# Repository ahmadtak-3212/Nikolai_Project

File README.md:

# Nikolai: electromagnet gauntlet

Nikolai is a 3D-printed gauntlet with a hand-wound **electromagnet in the palm**, so the wearer can pick up and hold ferromagnetic objects. It has three main parts:

- an ESP32 on the wrist that controls coil power with PWM and shows a touchscreen UI;
- a MOSFET coil driver that measures coil current and temperature;
- a small web server that stores per-user safety limits and logs sensor data.

It was a five-person team project for MIT **6.08** (Interconnected Embedded Systems) in spring 2022.

## Team

James Adams, Daven Howard, Sebastian Portalatin, **Ahmad Taka** and Colin Tang.

## Status

| Area | Status |
|---|---|
| Electrical | ✅ Coil driver v1 and v2 and the wrist PCB, all routed with Gerbers; schematic PDFs in `electrical/` |
| Firmware | ✅ `Firmware_V2` (PlatformIO, GUIslice touchscreen UI) is the final version; `Firmware_V1` is archived |
| Server | ✅ Worked on the class server; archived in `archive/Server` |
| Mechanical | ✅ Hand, forearm and coil mounts (SolidWorks), with STL and Ultimaker print files |

## Repository layout

```
nikolai_project/
├── electrical/
│   ├── coil_driver_v1/      KiCad 6 "maghand" (2-channel coil driver)
│   ├── coil_driver_v2/      KiCad 6 "maghand" (1-channel, smaller)
│   ├── wrist_pcb_v1/        KiCad 6 wrist board (ESP32 + display)
│   ├── Coil_Driver.pdf      coil driver schematic
│   └── Nikolai_Schematic.pdf  system schematic
├── firmware/Firmware_V2/    PlatformIO project (ESP32, final)
├── mechanical/
│   ├── cad/Nikolai.SLDASM   full assembly; Parts/{Hand,Forearm,Coil}
│   ├── exports/stl/         printable parts
│   └── cam/UMS3_*.3mf       Ultimaker S3 print projects (coil, forearm, hand)
├── archive/
│   ├── Firmware_V1/         first Arduino firmware + bring-up test sketches
│   ├── Server/              server.py, SQLite DB, web pages
│   └── Docs/Final Report/   full class write-up (Markdeep)
└── docs/images/             figures used below
```

## How it works

- **Power path:** a 3S LiPo powers the coil driver and the wrist board. The wrist board steps the battery down to 3.3 V with a switching regulator. The ripple was checked on a scope and was fine for the ESP32.
- **Control:** the ESP32 outputs **10 kHz, 8-bit PWM** to the coil driver's gate driver. The power level is set with a slider on the touchscreen.
- **Sensing:** coil current comes from a TI **TMCS1107** Hall-effect sensor. Its output maps about −2.8 to 27.7 A onto 0–3.3 V, and the firmware subtracts a measured bias of about −1.3 A. Coil temperature comes from a **DS18B20** 1-Wire sensor mounted in the coil housing.
- **Safety FSM:** if the current or temperature goes above the user's threshold, the firmware sets a fault flag, turns the coil off and locks the power slider at 0. The flag clears only after a sustained period of low current and low temperature.
- **Cloud sync:** the ESP32 regularly POSTs current and temperature readings for the selected user, and can pull that user's thresholds from the server (the "Sync" button).

## Hardware

### Coil

About **700 turns of 24 AWG** magnet wire, wound with a drill onto a custom 3D-printed bobbin with a **permalloy core**. The bobbin also mounts the coil to the palm and holds the temperature sensor and flyback diode. In testing the coil handled about **145 W for roughly 3 s** before heating became a concern.

### Coil driver (`electrical/coil_driver_v1`, `coil_driver_v2`)

| | v1 | v2 |
|---|---|---|
| Switch | 2 × **C3M0065090J** SiC MOSFET | 1 × C3M0065090J |
| Gate driver | **MCP14A0304** | MCP14A0304 |
| Current sense | 2 × **TMCS1107A1B** | 1 × TMCS1107A1B |
| Temperature | 2 × **DS18B20** | 1 × DS18B20 |
| Connectors | 2-pin battery input, 8-pin to wrist and coil | 2-pin battery input, 5-pin |
| Board | 2 layers, 48.3 × 55.9 mm | 2 layers, 30 × 45 mm |

The board has three ports: coil output and temperature-sensor input; power, PWM in and sensor data out to the ESP32; and the LiPo input.

### Wrist PCB (`electrical/wrist_pcb_v1`)

2 layers, 93.5 × 45.5 mm, all through-hole. The board has:

- two 1 × 19 sockets for a 38-pin **ESP32 dev board**;
- a 1 × 14 socket for the **ILI9341** touchscreen module;
- a 1 × 4 socket for the switching-regulator module;
- an 8-pin connector to the coil driver;
- a 2N3904/2N3906 transistor pair with a speaker;
- a screw terminal for the 12 V battery input.

### 3D-printed parts

A team member's hand, wrist and forearm were measured by hand, and mounts for each PCB and the coil were modeled around them in **SolidWorks 2021**. The parts were printed in **Tough PLA** on an Ultimaker S3.

## Firmware (`firmware/Firmware_V2`)

| Setting | Value |
|---|---|
| Board | `esp32dev` (Espressif32, Arduino framework), monitor at 115200 baud |
| Libraries | GUIslice ^0.17, TFT_eSPI ^2.4.61, OneWire ^2.3.6, DallasTemperature ^3.9.1, ArduinoJson ^6.19.4 |
| UI | GUIslice pages (Main, Settings with numeric keypad, User select, Power slider with live current and temperature meters, Sync and Wi-Fi buttons). The GUIslice Builder project is `guislice/guislice.prj`. |

| Pin | Function |
|---|---|
| GPIO 12 | Coil PWM out |
| GPIO 32 | DS18B20 data |
| GPIO 33 | Current sensor (ADC) |
| GPIO 14 | Battery voltage (ADC) |
| GPIO 16 | Display backlight |

```bash
cd firmware/Firmware_V2
pio run -t upload && pio device monitor
```

> **Before building:** TFT_eSPI reads its display and touch pins from its own `User_Setup.h`, and that file isn't in this repo. Configure it for an ILI9341 with touch and match your wiring. The Wi-Fi network and the server URL are hard-coded in `include/iot_server.h`, so point them at your own network and server.

## Server (`archive/Server`)

`server.py` is a single `request_handler(request)` script written for the 6.08 class server (`608dev-2.net`, sandbox `team73`). It stores data in SQLite (`dbs/nikolai.db`) using three tables:

| Table | Columns |
|---|---|
| `users` | time, user, password |
| `nikolai_data` | time, current, temperature, user |
| `settings` | time, user, power_lvl, curr_thresh, temp_thresh |

| Request | Purpose |
|---|---|
| `GET ?Uname=&Pass=` | Validate a login (used by `login.html`) |
| `GET ?visualize=true&Uname=[&time_start=&time_end=]` | Current and temperature history, plotted with Bokeh on `home.html` |
| `GET ?settings=true&Uname=` | Fetch a user's thresholds (used by the web page and by the ESP32 "Sync") |
| `POST Uname, Pass, current, temperature` | ESP32 sensor upload |
| `POST Uname, Pass, curr_thresh, temp_thresh` | Update thresholds from the web page or the ESP32 |

> This was a class demo. Passwords are stored and compared in plain text, so don't deploy it as-is.

## Reproducing

1. Wind the coil on the printed bobbin (`mechanical/exports/stl/Coil`) around a permalloy core, and fit the DS18B20 and a flyback diode.
2. Order or mill the coil driver and wrist boards from the Gerbers in each board folder (`g/` or `GBR/`). They open in KiCad 6 or newer.
3. Print the hand, forearm and coil mounts.
4. Host `server.py` on any Python server that calls `request_handler` with `method`, `args`, `values` and `form`. That is the 6.08 server convention; a small Flask wrapper also works.
5. Configure TFT_eSPI, set the server URL and Wi-Fi, and flash `Firmware_V2`.

The complete original write-up, with the API details, UI screenshots and the design discussion, is in [`archive/Docs/Final Report/README.md`](archive/Docs/Final%20Report/README.md).

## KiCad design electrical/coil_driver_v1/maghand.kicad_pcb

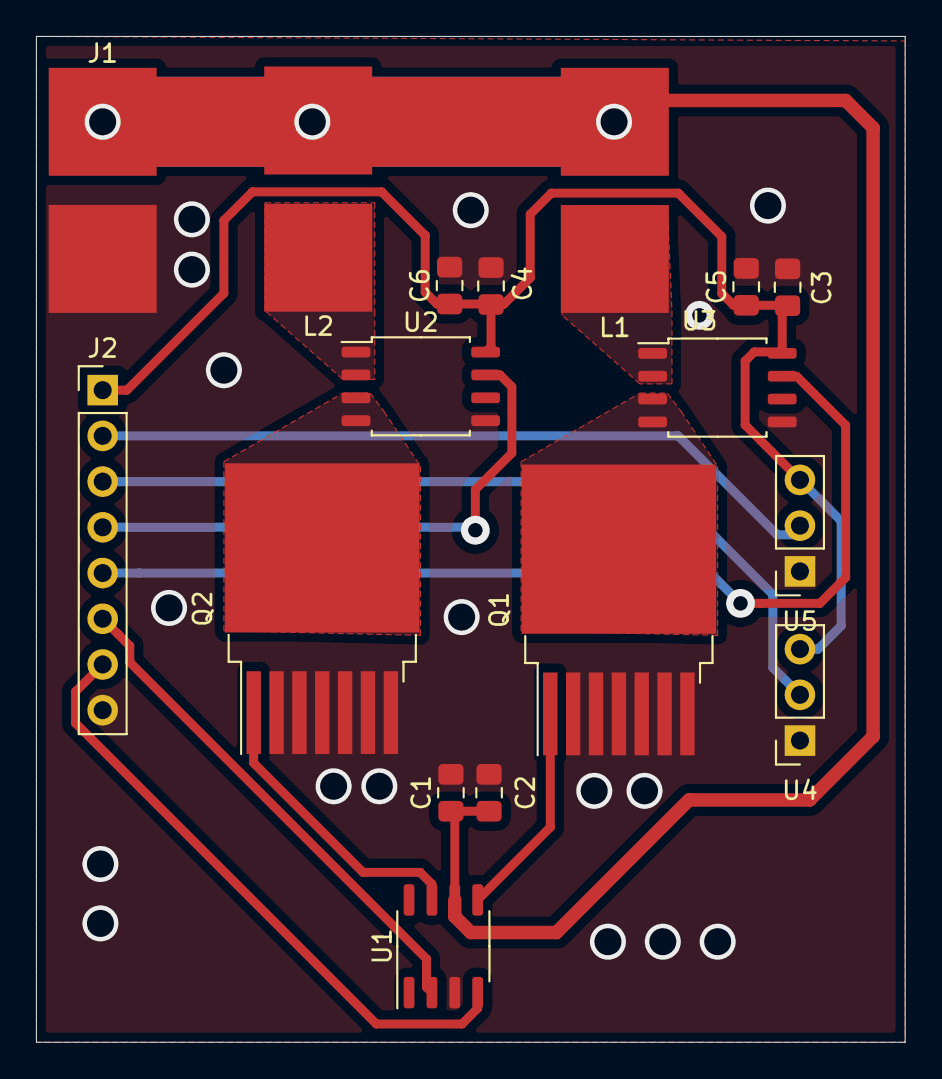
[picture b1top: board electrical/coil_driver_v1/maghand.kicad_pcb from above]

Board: 2 copper layers, 48.3 x 55.9 mm, 17 parts (0 on the bottom side), 15 nets.

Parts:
C1, C3, C4: .1 uF; C_0805_2012Metric_Pad1.15x1.40mm_HandSolder
C2, C5, C6: 1 uF; C_0805_2012Metric_Pad1.15x1.40mm_HandSolder
J1: Conn_01x02_Female; 2x6mmsquare
J2: Conn_01x08_Male; PinHeader_1x08_P2.54mm_Vertical
L1, L2: INDUCTOR; 2x6mmsquare
Q1, Q2: C3M0065090J; TO-263-7_TabPin8
U1: MCP14A0304xMNY; SO-8_3.9x4.9mm_P1.27mm
U2, U3: TMCS1107A1BQDR; SOIC-8_5.23x5.23mm_P1.27mm
U4, U5: DS18B20; PinSocket_1x03_P2.54mm_Vertical

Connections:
+3V3: C3.1, C4.1, C5.1, C6.1, J2.1, U2.8, U3.8, U4.3, U5.3
+12V: C1.1, C2.1, J1.1, L1.2, L2.2, U1.6
A_CUR: J2.4, U2.7
A_TEMP: J2.2, U5.2
B_CUR: J2.5, U3.7
B_TEMP: J2.3, U4.2
GND: C1.2, C2.2, C3.2, C4.2, C5.2, C6.2, J1.2, J2.8, Q1.2, Q1.3, Q1.4, Q1.5, Q1.6, Q1.7, Q2.2, Q2.3, Q2.4, Q2.5, Q2.6, Q2.7, U1.3, U2.5, U3.5, U4.1, U5.1
IN_A: J2.6, U1.2
IN_B: J2.7, U1.4
unnamed: L1.1, U3.1, U3.2
unnamed: L2.1, U2.1, U2.2
unnamed: Q1.1, U1.5
unnamed: Q1.8, U3.3, U3.4
unnamed: Q2.1, U1.7
unnamed: Q2.8, U2.3, U2.4

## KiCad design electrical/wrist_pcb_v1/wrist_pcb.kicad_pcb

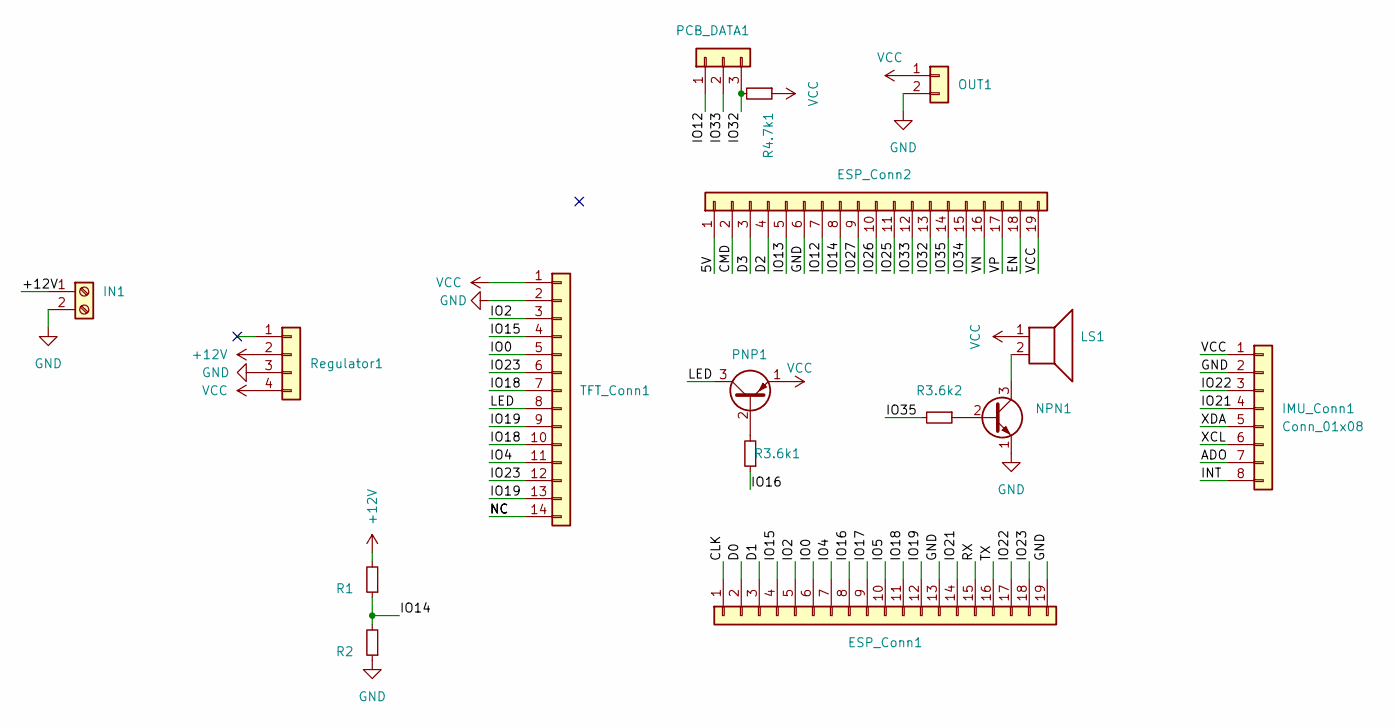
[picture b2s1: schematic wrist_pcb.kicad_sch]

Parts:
ESP_Conn1, ESP_Conn2: Conn_01x19; PinSocket_1x19_P2.54mm_Vertical
IMU_Conn1: Conn_01x08; PinSocket_1x08_P2.54mm_Vertical
IN1: Screw_Terminal_01x02; TerminalBlock_bornier-2_P5.08mm
LS1: Speaker; R_Axial_DIN0207_L6.3mm_D2.5mm_P7.62mm_Horizontal
NPN1: (no value)
OUT1: Conn_01x02; PinHeader_1x02_P2.54mm_Horizontal
PCB_DATA1: Conn_01x03; PinHeader_1x03_P2.54mm_Horizontal
PNP1: 2N3906
R1, R2, R3.6k1, R3.6k2, R4.7k1: R_Small; R_Axial_DIN0207_L6.3mm_D2.5mm_P7.62mm_Horizontal
Regulator1: Conn_01x04; PinSocket_1x04_P2.54mm_Vertical
TFT_Conn1: Conn_01x14; PinSocket_1x14_P2.54mm_Vertical

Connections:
+12V: IN1.1, R1.2, Regulator1.2
/5V: ESP_Conn2.1
/ADO: IMU_Conn1.7
/CLK: ESP_Conn1.1
/CMD: ESP_Conn2.2
/D0: ESP_Conn1.2
/D1: ESP_Conn1.3
/D2: ESP_Conn2.4
/D3: ESP_Conn2.3
/EN: ESP_Conn2.18
/INT: IMU_Conn1.8
/IO0: ESP_Conn1.6, TFT_Conn1.5
/IO2: ESP_Conn1.5, TFT_Conn1.3
/IO4: ESP_Conn1.7, TFT_Conn1.11
/IO5: ESP_Conn1.10
/IO12: ESP_Conn2.7, PCB_DATA1.1
/IO13: ESP_Conn2.5
/IO14: ESP_Conn2.8, R1.1, R2.2
/IO15: ESP_Conn1.4, TFT_Conn1.4
/IO16: ESP_Conn1.8, R3.6k1.1
/IO17: ESP_Conn1.9
/IO18: ESP_Conn1.11, TFT_Conn1.7, TFT_Conn1.10
/IO19: ESP_Conn1.12, TFT_Conn1.9, TFT_Conn1.13
/IO21: ESP_Conn1.14, IMU_Conn1.4
/IO22: ESP_Conn1.17, IMU_Conn1.3
/IO23: ESP_Conn1.18, TFT_Conn1.6, TFT_Conn1.12
/IO25: ESP_Conn2.11
/IO26: ESP_Conn2.10
/IO27: ESP_Conn2.9
/IO32: ESP_Conn2.13, PCB_DATA1.3, R4.7k1.2
/IO33: ESP_Conn2.12, PCB_DATA1.2
/IO34: ESP_Conn2.15
/IO35: ESP_Conn2.14, R3.6k2.2
/LED: PNP1.3 (C), TFT_Conn1.8
/NC: TFT_Conn1.14
/RX: ESP_Conn1.15
/TX: ESP_Conn1.16
/VN: ESP_Conn2.16
/VP: ESP_Conn2.17
/XCL: IMU_Conn1.6
/XDA: IMU_Conn1.5
GND: ESP_Conn1.13, ESP_Conn1.19, ESP_Conn2.6, IMU_Conn1.2, IN1.2 (Pin_1), NPN1.1 (E), OUT1.2, R2.1, Regulator1.3, TFT_Conn1.2
unnamed: LS1.2, NPN1.3 (C)
unnamed: NPN1.2 (B), R3.6k2.1
unnamed: PNP1.2 (B), R3.6k1.2
VCC: ESP_Conn2.19, IMU_Conn1.1, LS1.1, OUT1.1, PNP1.1 (E), R4.7k1.1, Regulator1.4, TFT_Conn1.1

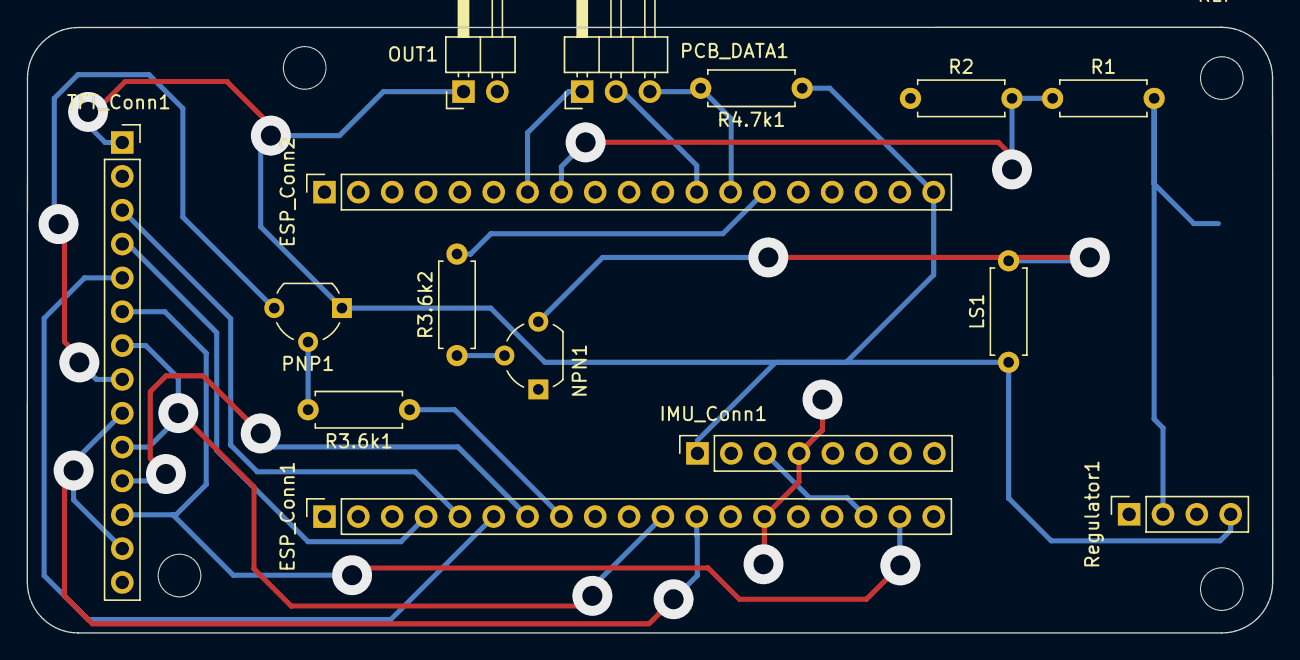
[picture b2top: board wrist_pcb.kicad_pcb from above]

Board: 2 copper layers, 93.5 x 45.5 mm, 16 parts (1 on the bottom side), 22 nets.

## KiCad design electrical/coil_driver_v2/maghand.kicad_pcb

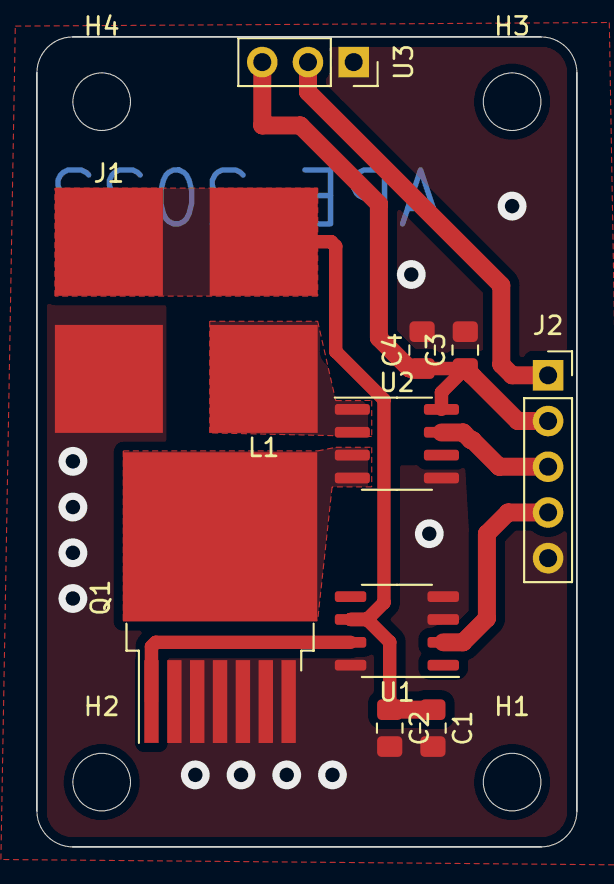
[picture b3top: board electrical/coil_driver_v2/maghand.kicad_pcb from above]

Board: 2 copper layers, 30.0 x 45.0 mm, 15 parts (0 on the bottom side), 9 nets.

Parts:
C1, C3: .1 uF; C_0805_2012Metric_Pad1.15x1.40mm_HandSolder
C2, C4: 1 uF; C_0805_2012Metric_Pad1.15x1.40mm_HandSolder
H1, H2, H3, H4: MountingHole_Pad; MountingHole_3.2mm_M3
J1: Conn_01x02_Female; 2x6mmsquare
J2: Conn_01x05_Male; PinSocket_1x05_P2.54mm_Vertical
L1: INDUCTOR; 2x6mmsquare
Q1: C3M0065090J; TO-263-7_TabPin8
U1: MCP14A0304xMNY; SO-8_3.9x4.9mm_P1.27mm
U2: TMCS1107A1BQDR; SOIC-8_3.9x4.9mm_P1.27mm
U3: DS18B20; PinSocket_1x03_P2.54mm_Vertical

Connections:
+3V3: C3.1, C4.1, J2.2, U2.8, U3.3
+12V: C1.1, C2.1, J1.1, L1.2, U1.6
A_CUR: J2.3, U2.7
A_TEMP: J2.1, U3.2
GND: C1.2, C2.2, C3.2, C4.2, J1.2, J2.5, Q1.2, Q1.3, Q1.4, Q1.5, Q1.6, Q1.7, U1.3, U1.4, U1.8, U2.5, U3.1
IN_A: J2.4, U1.2
unnamed: L1.1, U2.1, U2.2
unnamed: Q1.1, U1.7
unnamed: Q1.8, U2.3, U2.4

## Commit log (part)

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2022-06-26 Readme
